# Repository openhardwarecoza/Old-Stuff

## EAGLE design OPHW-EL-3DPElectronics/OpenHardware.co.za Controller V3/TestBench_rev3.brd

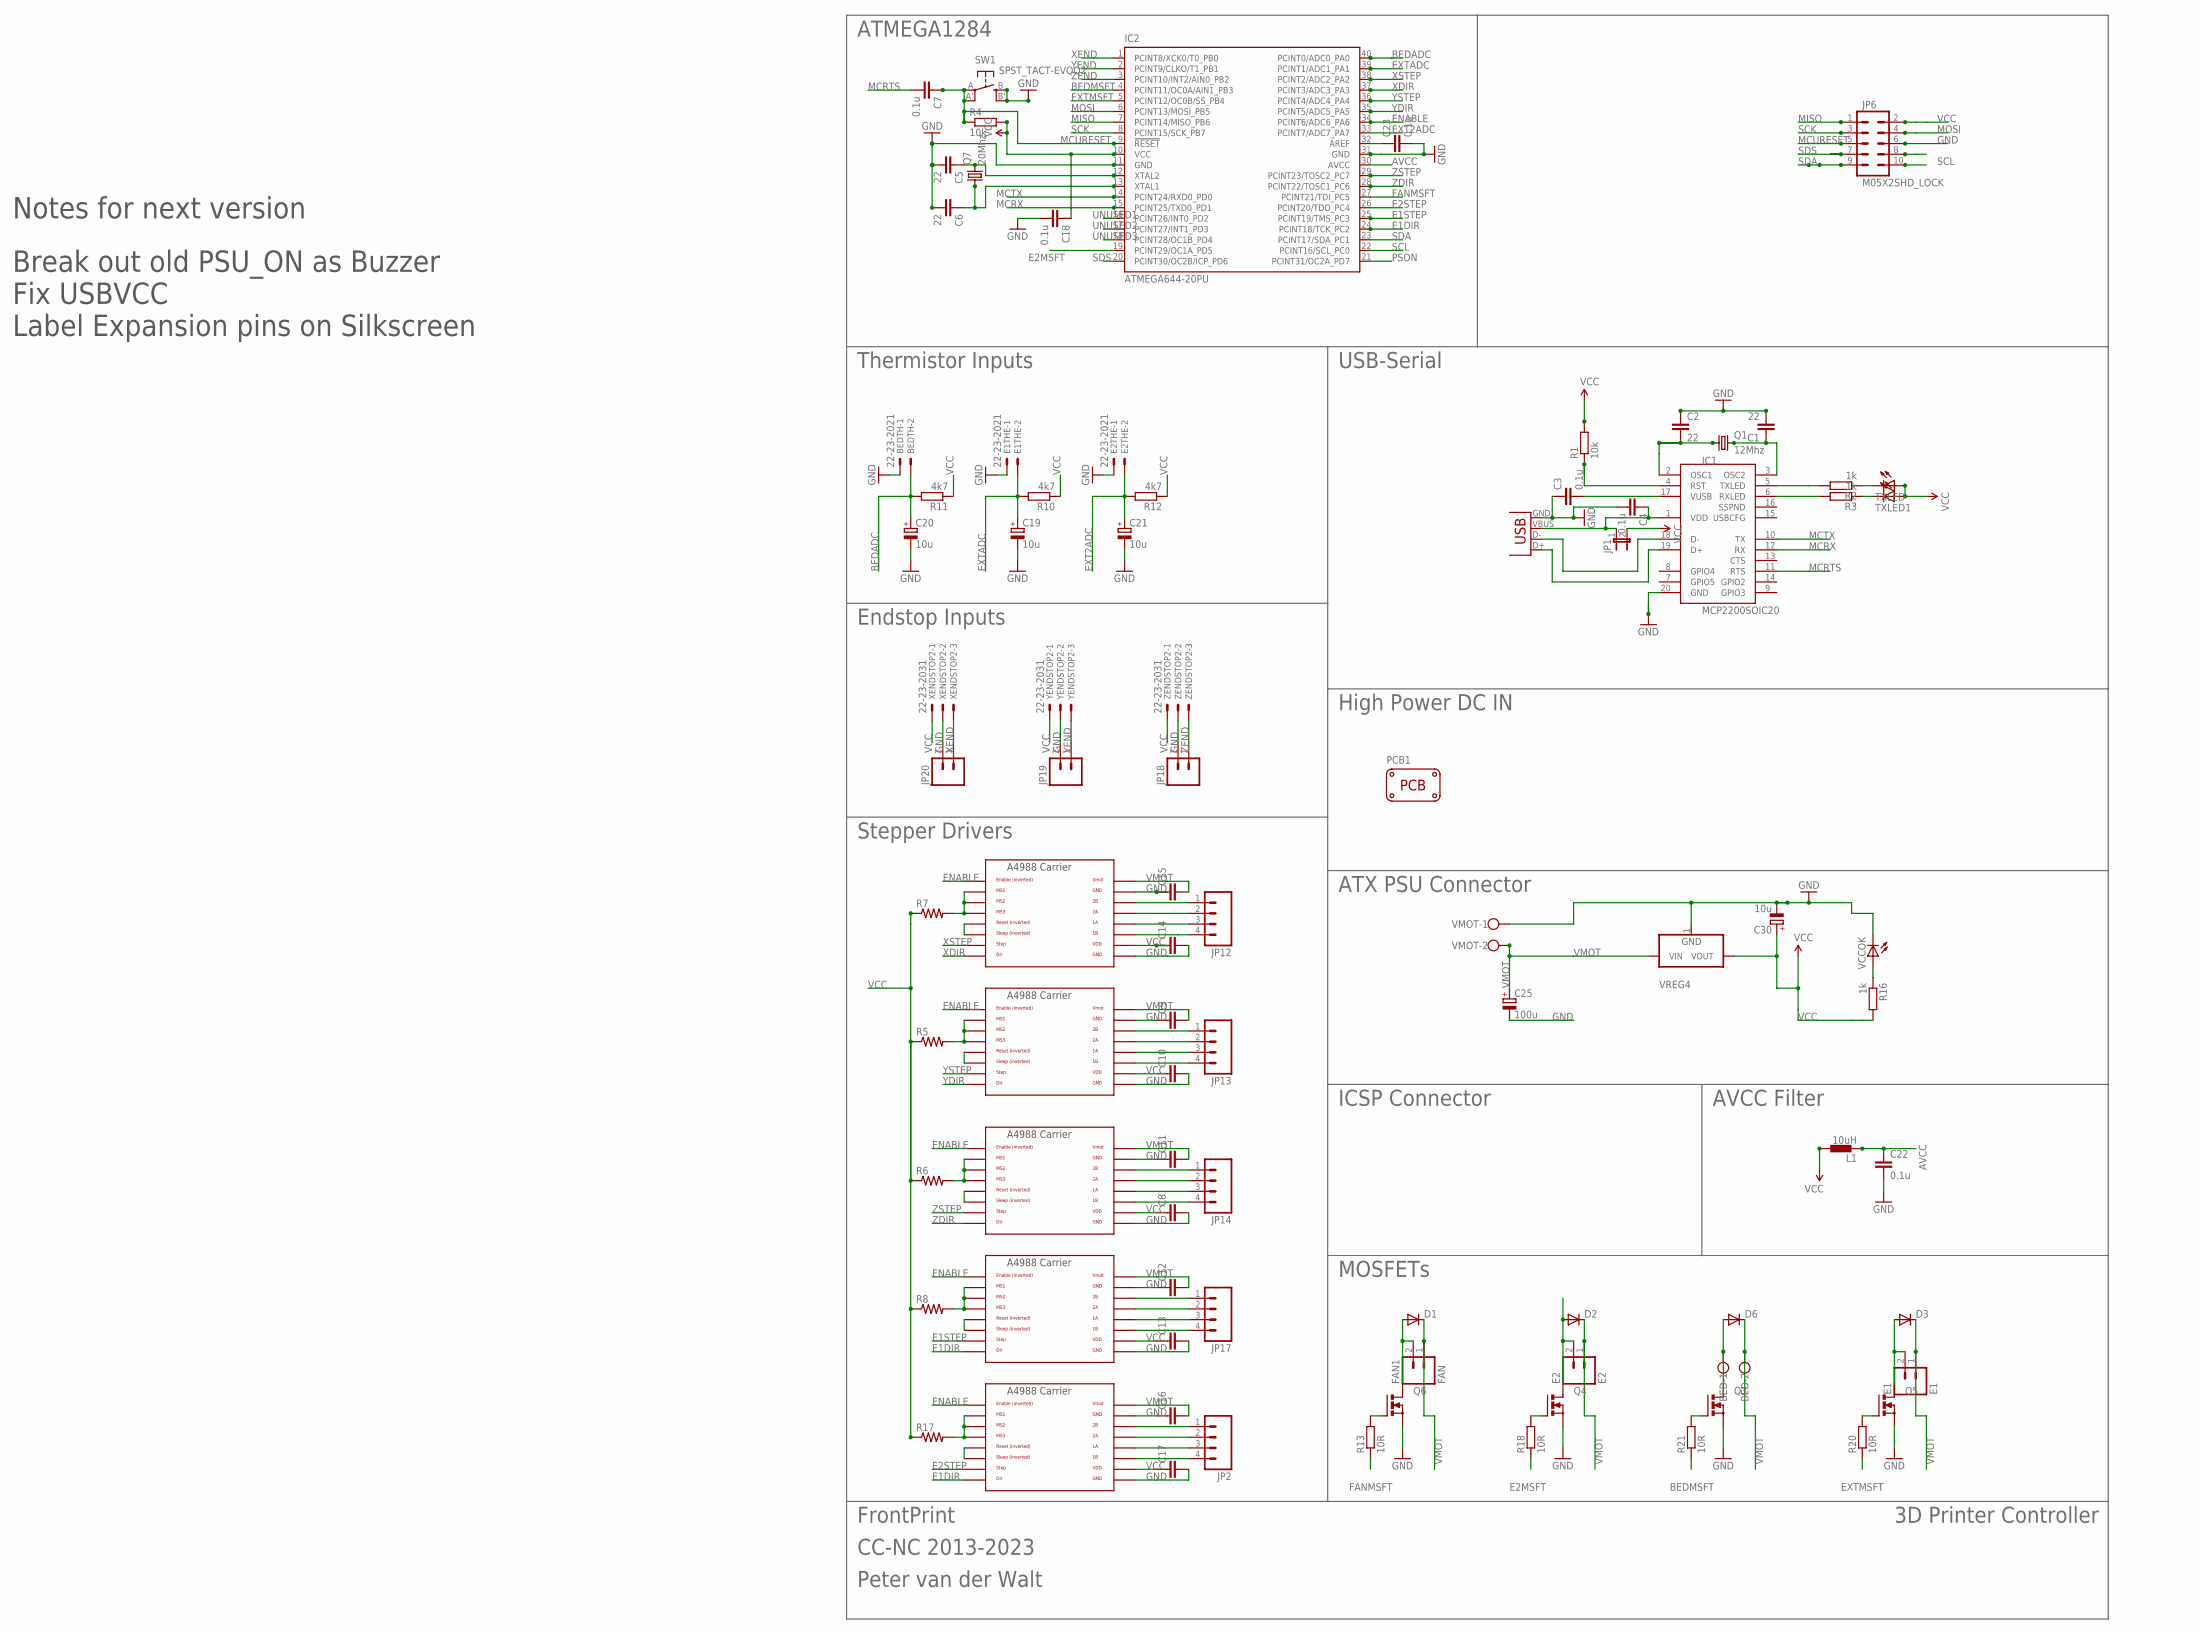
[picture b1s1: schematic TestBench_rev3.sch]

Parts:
BED: W237-102
BEDTH: 22-23-2021
C1, C2, C5, C6: 22; 1206
C3, C4, C7, C18, C22, C23: 0.1u; 1206
C8, C9, C10, C11, C12, C13, C14, C15, C16, C17: CAP1206; 1206
C19, C20, C21: 10u; E2,5-5
C25: 100u; E5-8,5
C30: 10u; E2-5
D1, D2, D3, D6: DIODESMA-ALT; SMA-DIODE_ALT
E1: E1; SCREWTERMINAL-3.5MM-2
E1POL, E2POL: POLOLU_A4983CARRIER; A4988BREAKOUT
E1THE, E2THE: 22-23-2021
E2: E2; SCREWTERMINAL-3.5MM-2
FAN1: FAN; SCREWTERMINAL-3.5MM-2
IC1: MCP2200SOIC20; SOIC20
IC2: ATMEGA644-20PU; DIL40
JP1: JUMPER-2PTH_LOCK; 1X02_LOCK
JP2, JP12, JP13, JP14, JP17: M04SCREW; SCREWTERMINAL-3.5MM-4
JP6: M05X2SHD_LOCK; 2X5-SHROUDED_LOCK
JP18, JP19, JP20: M023.5MM; SCREWTERMINAL-3.5MM-2
L1: 10uH; BL01RN1A
PCB1: PCB_DP_SQUARE-10X10; DP100100_V1
Q1: 12Mhz; HC49UP
Q3, Q4, Q5, Q6: PMOSFET_NTO220BV; TO220BV
Q7: 20Mhz; HC49UP
R1, R4: 10k; M1206
R2, R3, R16: 1k; M1206
R5, R6, R7, R8, R17: RESISTOR1206; 1206
R10, R11, R12: 4k7; M1206
R13, R18, R20, R21: 10R; M1206
SW1: SPST_TACT-EVQQ2; EVQ-Q2
TXLED, TXLED1: LEDSMT1206; 1206
VCCOK: LEDSMT1206; 1206
VMOT: W237-102; MPN 237-102
VREG4: VREG_3PINS-DPAK; DPAK
X1: USBPTH; USB-B-PTH
XENDSTOP2: 22-23-2031
XPOL: POLOLU_A4983CARRIER; A4988BREAKOUT
YENDSTOP2: 22-23-2031
YPOL: POLOLU_A4983CARRIER; A4988BREAKOUT
ZENDSTOP2: 22-23-2031
ZPOL: POLOLU_A4983CARRIER; A4988BREAKOUT

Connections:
AVCC: C22.1, IC2.30 (AVCC), L1.1
BEDADC: BEDTH.2, C20.+, IC2.40 (PCINT0/ADC0_PA0), R11.2
BEDMSFT: IC2.4 (PCINT11/OC0A/AIN1_PB3), R21.1
BEDOUT1: BED.1, D6.A, Q3.D
BEDOUT2: D3.A, E1.2, Q5.D
E1DIR: E1POL.DIR, E2POL.DIR, IC2.24 (PCINT18/TCK_PC2)
E1OUT1: D2.A, E2.2, Q4.D
E1STEP: E1POL.STEP, IC2.25 (PCINT19/TMS_PC3)
E2MSFT: IC2.19 (PCINT29/OC1A_PD5), R18.1
E2STEP: E2POL.STEP, IC2.26 (PCINT20/TDO_PC4)
ENABLE: E1POL.EN, E2POL.EN, IC2.34 (PCINT6/ADC6_PA6), XPOL.EN, YPOL.EN, ZPOL.EN
EXT2ADC: C21.+, E2THE.2, IC2.33 (PCINT7/ADC7_PA7), R12.2
EXTADC: C19.+, E1THE.2, IC2.39 (PCINT1/ADC1_PA1), R10.2
EXTMSFT: IC2.5 (PCINT12/OC0B/SS_PB4), R20.1
FANMSFT: IC2.27 (PCINT21/TDI_PC5), R13.1
FANOUT1: D1.A, FAN1.2, Q6.D
GND: BEDTH.1, C1.2, C2.1, C3.1, C4.2, C5.2, C6.2, C8.2, C9.1, C10.2, C11.1, C12.1, C13.2, C14.2, C15.1, C16.1, C17.2, C18.2, C19.-, C20.-, C21.-, C22.2, C23.2, C25.-, C30.-, E1POL.GND, E1POL.GND@0 (GND), E1THE.1, E2POL.GND, E2POL.GND@0 (GND), E2THE.1, IC1.20 (GND), IC2.11 (GND), IC2.31 (GND), JP6.6, JP18.2, JP19.2, JP20.2, Q3.S, Q4.S, Q5.S, Q6.S, SW1.B (S), SW1.B' (S1), VCCOK.C, VMOT.1, VREG4.1 (GND), X1.GND, XENDSTOP2.2, XPOL.GND, XPOL.GND@0 (GND), YENDSTOP2.2, YPOL.GND, YPOL.GND@0 (GND), ZENDSTOP2.2, ZPOL.GND, ZPOL.GND@0 (GND)
MCRTS: C7.2, IC1.11 (RTS)
MCRX: IC1.12 (RX), IC2.15 (PCINT25/TXD0_PD1)
MCTX: IC1.10 (TX), IC2.14 (PCINT24/RXD0_PD0)
MCURESET: C7.1, IC2.9 (!RESET), JP6.5, R4.1, SW1.A, SW1.A' (P1)
MISO: IC2.7 (PCINT14/MISO_PB6), JP6.1
MOSI: IC2.6 (PCINT13/MOSI_PB5), JP6.4
unnamed: C2.2, IC1.2 (OSC1), Q1.1
unnamed: C1.1, IC1.3 (OSC2), Q1.2
unnamed: IC1.5 (TXLED), R2.2
unnamed: IC1.18 (D-), X1.D-
unnamed: IC1.19 (D+), X1.D+
unnamed: IC1.6 (RXLED), R3.2
unnamed: C3.2, IC1.17 (VUSB)
unnamed: E2POL.RST, E2POL.SLP (SLEEP)
unnamed: R2.1, TXLED.C
unnamed: R3.1, TXLED1.C
unnamed: C5.1, IC2.12 (XTAL2), Q7.2
unnamed: C6.1, IC2.13 (XTAL1), Q7.1
unnamed: IC1.4 (RST), R1.1
unnamed: E1POL.RST, E1POL.SLP (SLEEP)
unnamed: ZPOL.RST, ZPOL.SLP (SLEEP)
unnamed: YPOL.RST, YPOL.SLP (SLEEP)
unnamed: XPOL.RST, XPOL.SLP (SLEEP)
unnamed: R7.2, XPOL.MS1, XPOL.MS2, XPOL.MS3
unnamed: R5.2, YPOL.MS1, YPOL.MS2, YPOL.MS3
unnamed: E1POL.MS1, E1POL.MS2, E1POL.MS3, R8.2
unnamed: R6.2, ZPOL.MS1, ZPOL.MS2, ZPOL.MS3
unnamed: E1POL.1B, JP17.4
unnamed: E1POL.1A, JP17.3
unnamed: E1POL.2A, JP17.2
unnamed: E1POL.2B, JP17.1
unnamed: JP14.4, ZPOL.1B
unnamed: JP14.3, ZPOL.1A
unnamed: JP14.2, ZPOL.2A
unnamed: JP14.1, ZPOL.2B
unnamed: JP13.1, YPOL.2B
unnamed: JP13.2, YPOL.2A
unnamed: JP13.3, YPOL.1A
unnamed: JP13.4, YPOL.1B
unnamed: JP12.4, XPOL.1B
unnamed: JP12.3, XPOL.1A
unnamed: JP12.2, XPOL.2A
unnamed: JP12.1, XPOL.2B
unnamed: E2POL.MS1, E2POL.MS2, E2POL.MS3, R17.2
unnamed: E2POL.1B, JP2.4
unnamed: E2POL.1A, JP2.3
unnamed: E2POL.2A, JP2.2
unnamed: E2POL.2B, JP2.1
unnamed: Q5.G, R20.2
unnamed: C23.1, IC2.32 (AREF)
unnamed: Q6.G, R13.2
unnamed: C4.1, IC1.1 (VDD), JP1.1, X1.VBUS
unnamed: Q4.G, R18.2
unnamed: R16.1, VCCOK.A
unnamed: Q3.G, R21.2
PSON: IC2.21 (PCINT31/OC2A_PD7)
SCK: IC2.8 (PCINT15/SCK_PB7), JP6.3
SCL: IC2.22 (PCINT16/SCL_PC0), JP6.10
SDA: IC2.23 (PCINT17/SDA_PC1), JP6.9
SDS: IC2.20 (PCINT30/OC2B/ICP_PD6), JP6.7
UNUSED1: IC2.16 (PCINT26/INT0_PD2)
UNUSED2: IC2.17 (PCINT27/INT1_PD3)
UNUSED3: IC2.18 (PCINT28/OC1B_PD4)
VCC: C8.1, C10.1, C13.1, C14.1, C17.1, C18.1, C30.+, E1POL.VDD, E2POL.VDD, IC2.10 (VCC), JP1.2, JP6.2, L1.2, R1.2, R4.2, R5.1, R6.1, R7.1, R8.1, R10.1, R11.1, R12.1, R16.2, R17.1, TXLED.A, TXLED1.A, VREG4.2 (VOUT), XENDSTOP2.1, XPOL.VDD, YENDSTOP2.1, YPOL.VDD, ZENDSTOP2.1, ZPOL.VDD
VMOT: BED.2, C9.2, C11.2, C12.2, C15.2, C16.2, C25.+, D1.C, D2.C, D3.C, D6.C, E1.1, E1POL.VMOT, E2.1, E2POL.VMOT, FAN1.1, VMOT.2, VREG4.3 (VIN), XPOL.VMOT, YPOL.VMOT, ZPOL.VMOT
XDIR: IC2.37 (PCINT3/ADC3_PA3), XPOL.DIR
XEND: IC2.1 (PCINT8/XCK0/T0_PB0), JP20.1, XENDSTOP2.3
XSTEP: IC2.38 (PCINT2/ADC2_PA2), XPOL.STEP
YDIR: IC2.35 (PCINT5/ADC5_PA5), YPOL.DIR
YEND: IC2.2 (PCINT9/CLKO/T1_PB1), JP19.1, YENDSTOP2.3
YSTEP: IC2.36 (PCINT4/ADC4_PA4), YPOL.STEP
ZDIR: IC2.28 (PCINT22/TOSC1_PC6), ZPOL.DIR
ZEND: IC2.3 (PCINT10/INT2/AIN0_PB2), JP18.1, ZENDSTOP2.3
ZSTEP: IC2.29 (PCINT23/TOSC2_PC7), ZPOL.STEP

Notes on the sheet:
Thermistor Inputs
Endstop Inputs
Stepper Drivers
USB-Serial
AVCC Filter
ATX PSU Connector
ICSP Connector
MOSFETs
High Power DC IN
ATMEGA1284
FrontPrint
CC-NC 2013-2023
Peter van der Walt
3D Printer Controller
Notes for next version
Break out old PSU_ON as Buzzer
Fix USBVCC
Label Expansion pins on Silkscreen

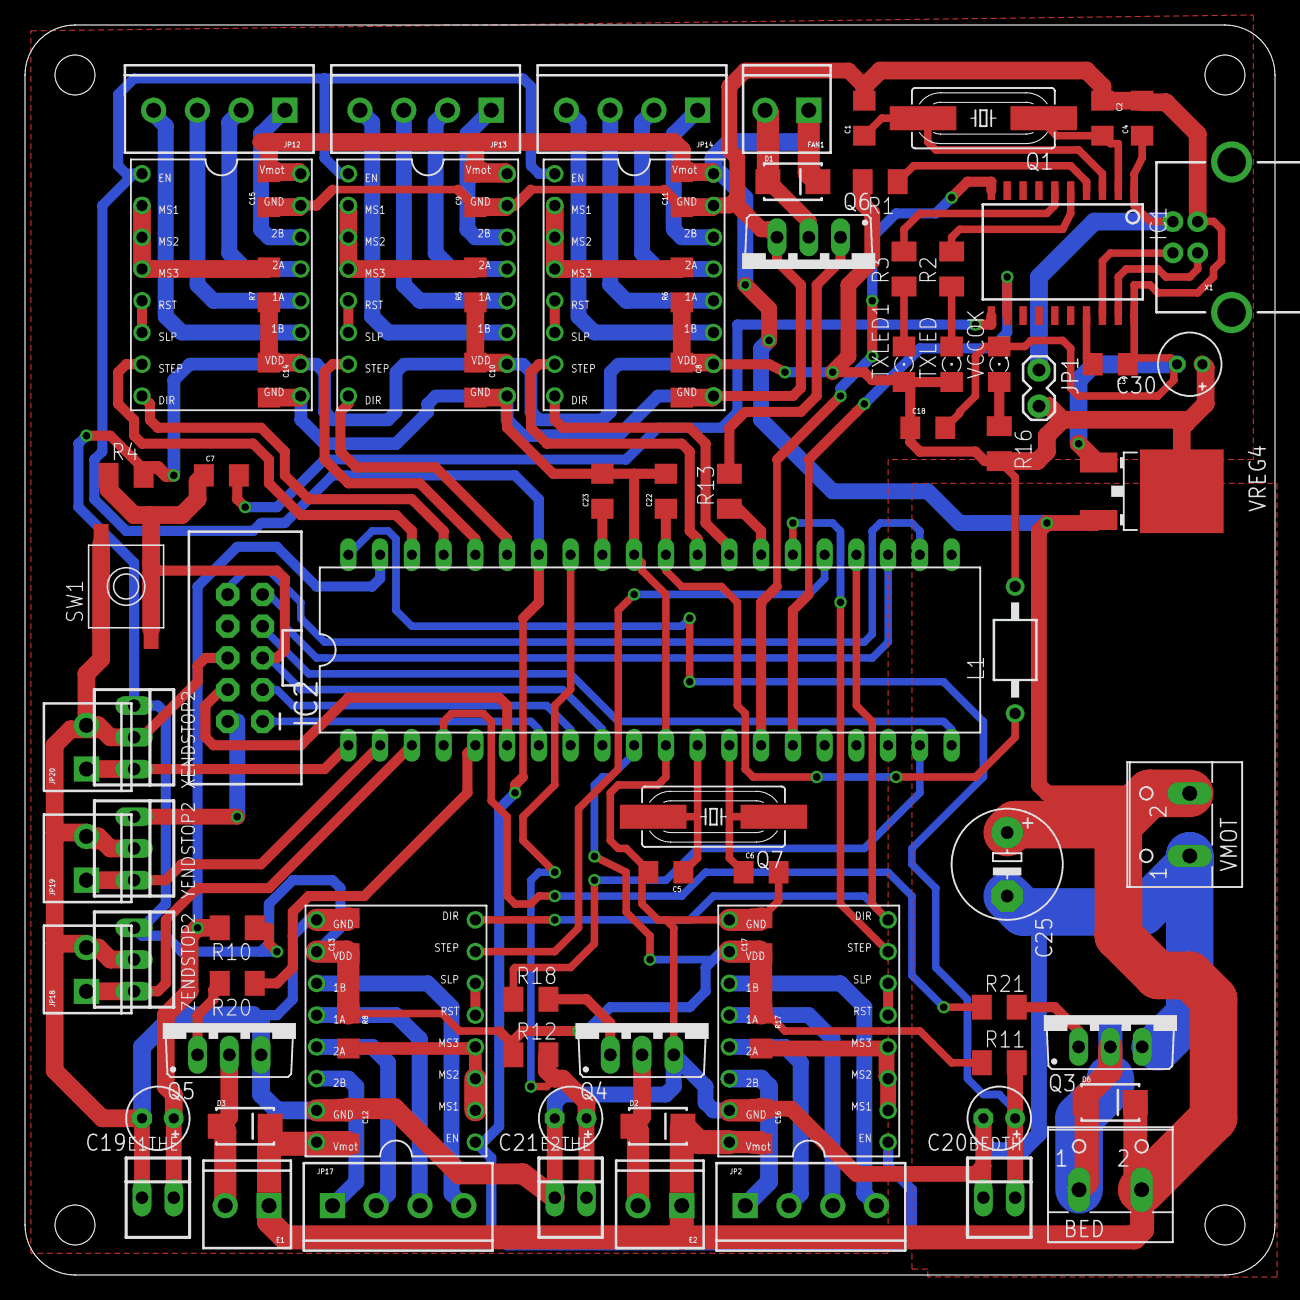
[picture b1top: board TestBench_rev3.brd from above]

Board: 2 copper layers, 100.0 x 100.0 mm, 88 parts (0 on the bottom side), 87 nets.

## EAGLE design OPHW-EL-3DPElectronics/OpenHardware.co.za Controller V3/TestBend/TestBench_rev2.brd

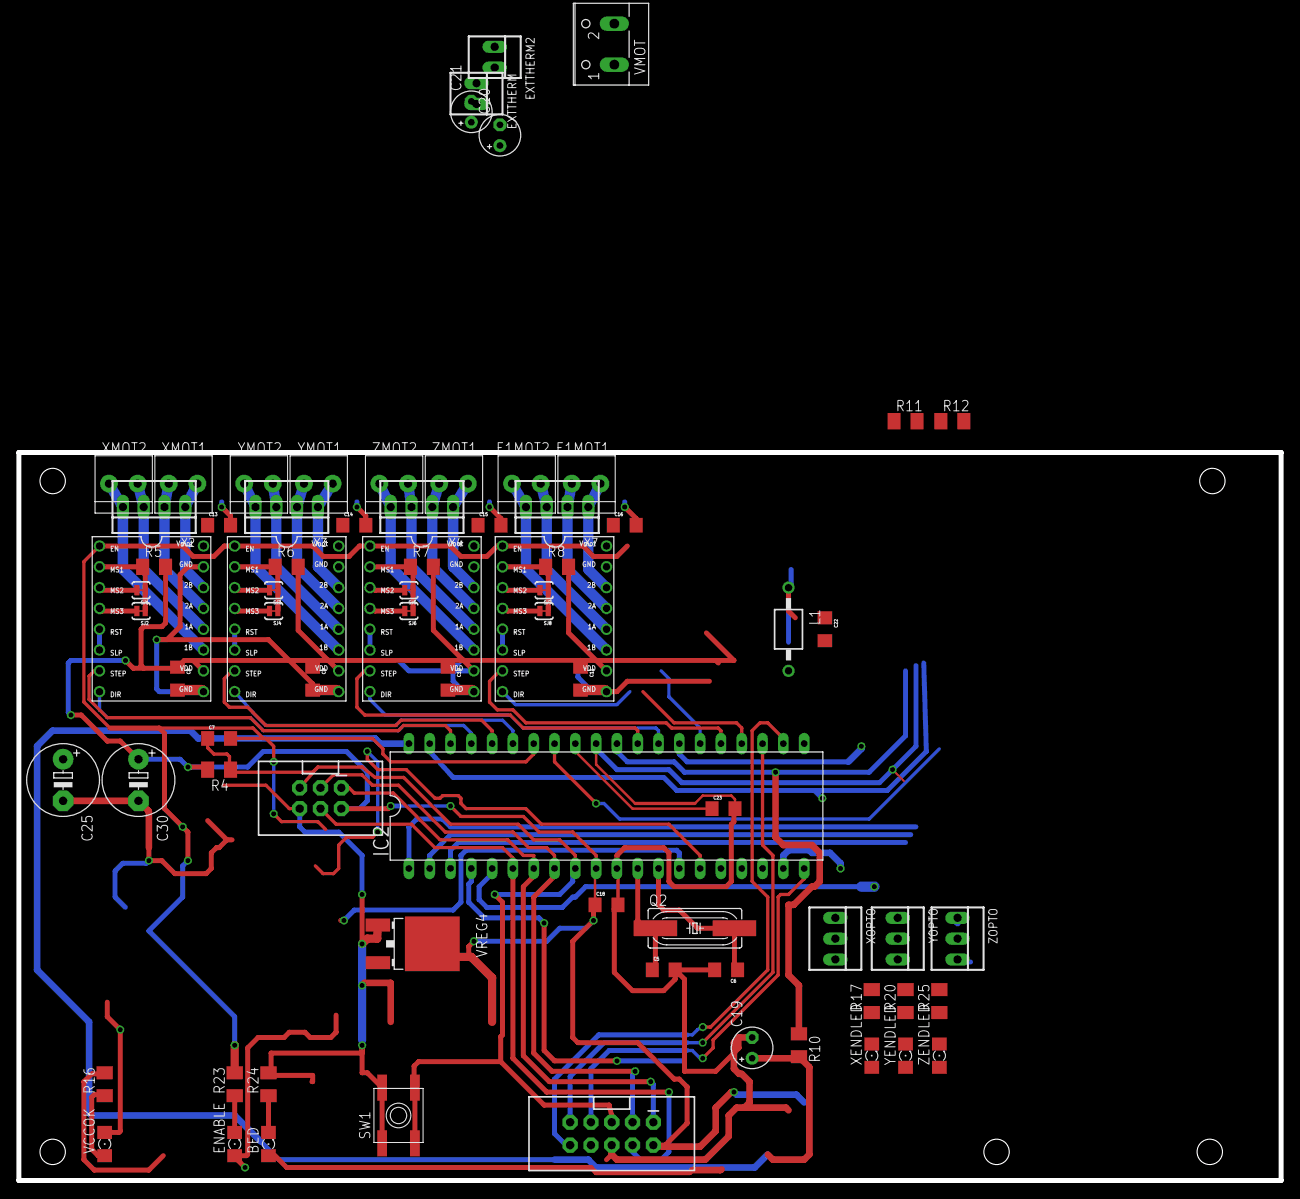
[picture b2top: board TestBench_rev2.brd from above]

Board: 2 copper layers, 154.1 x 88.9 mm, 81 parts (0 on the bottom side), 68 nets.

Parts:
BED: 1206
C5, C6: 22; 1206
C7, C8, C9, C10, C11, C13, C14, C15, C16, C18, C22, C23: 0.1u; 1206
C19, C20, C21: 10u; E2,5-5
C25, C30: 100u; E5-8,5
E1MOT1, E1MOT2: 1X2-3.5MM; 3.5MMTERM
ENABLE: 1206
EPOLOLU: POLOLU_A4983CARRIER; A4988BREAKOUT
EXTTHERM, EXTTHERM2: 22-23-2021
IC2: ATMEGA644-20PU; DIL40
J2: 2X3-SHROUDED
L1: 10uH; BL01RN1A
LCDCONNECTOR: M05X2SHD_LOCK; 2X5-SHROUDED_LOCK
Q2: 20mHz; HC49UP
R4: 10k; M1206
R5, R6, R7, R8: 1K; M1206
R10, R11, R12: 4k7; M1206
R16, R17, R20, R23, R24, R25: 1k; M1206
SJ1, SJ2, SJ3, SJ4, SJ5, SJ6, SJ7, SJ8: SOLDERJUMPERTRACE; SJ_2S-TRACE
SW1: SPST_TACT-EVQQ2; EVQ-Q2
U$1, U$5, U$6, U$7, U$8: 3MMHOLE
VCCOK: 1206
VMOT: W237-102
VREG4: DPAK
X2, X3, X4, X7: 22-23-2041
XENDLED: 1206
XMOT1, XMOT2: 1X2-3.5MM; 3.5MMTERM
XOPTO: 22-23-2031
XPOLOLU: POLOLU_A4983CARRIER; A4988BREAKOUT
YENDLED: 1206
YMOT1, YMOT2: 1X2-3.5MM; 3.5MMTERM
YOPTO: 22-23-2031
YPOLOLU: POLOLU_A4983CARRIER; A4988BREAKOUT
ZENDLED: 1206
ZMOT1, ZMOT2: 1X2-3.5MM; 3.5MMTERM
ZOPTO: 22-23-2031
ZPOLOLU: POLOLU_A4983CARRIER; A4988BREAKOUT

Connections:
AVCC: C22.1, IC2.30, L1.1, R10.1, R11.1, R12.1
BEDADC: C19.+, IC2.40, R10.2
BEDMSFT: BED.A, IC2.4
E1DIR: EPOLOLU.DIR, IC2.24
E1STEP: EPOLOLU.STEP, IC2.25
E11A: E1MOT2.1, EPOLOLU.1A, X7.3
E11B: E1MOT2.2, EPOLOLU.1B, X7.4
E12A: E1MOT1.2, EPOLOLU.2A, X7.2
E12B: E1MOT1.1, EPOLOLU.2B, X7.1
ENABLE: EPOLOLU.EN, IC2.34, R23.2, XPOLOLU.EN, YPOLOLU.EN, ZPOLOLU.EN
EXT2ADC: C21.+, EXTTHERM2.2, IC2.33, R12.2
EXTADC: C20.+, EXTTHERM.2, IC2.39, R11.2
GND: C5.2, C6.2, C8.2, C9.2, C10.2, C11.2, C13.2, C14.2, C15.2, C16.2, C18.2, C19.-, C20.-, C21.-, C22.2, C23.2, C25.-, C30.-, EPOLOLU.GND, EPOLOLU.GND@0, EXTTHERM.1, EXTTHERM2.1, IC2.11, IC2.31, J2.6, LCDCONNECTOR.6, R24.2, SW1.B, SW1.B', VCCOK.C, VMOT.1, VREG4.1, XOPTO.2, XPOLOLU.GND, XPOLOLU.GND@0, YOPTO.2, YPOLOLU.GND, YPOLOLU.GND@0, ZOPTO.2, ZPOLOLU.GND, ZPOLOLU.GND@0
MCURESET: C7.1, IC2.9, J2.5, LCDCONNECTOR.5, R4.1, SW1.A, SW1.A'
MISO: IC2.7, J2.1, LCDCONNECTOR.1
MOSI: IC2.6, J2.4, LCDCONNECTOR.4
unnamed: C5.1, IC2.12, Q2.1
unnamed: C6.1, IC2.13, Q2.2
unnamed: R7.1, SJ5.1, SJ6.1, ZPOLOLU.MS1
unnamed: SJ6.2, ZPOLOLU.MS3
unnamed: SJ5.2, ZPOLOLU.MS2
unnamed: EPOLOLU.MS2, SJ7.2
unnamed: EPOLOLU.MS3, SJ8.2
unnamed: EPOLOLU.MS1, R8.1, SJ7.1, SJ8.1
unnamed: SJ3.2, YPOLOLU.MS2
unnamed: SJ4.2, YPOLOLU.MS3
unnamed: R6.1, SJ3.1, SJ4.1, YPOLOLU.MS1
unnamed: SJ1.2, XPOLOLU.MS2
unnamed: SJ2.2, XPOLOLU.MS3
unnamed: R5.1, SJ1.1, SJ2.1, XPOLOLU.MS1
unnamed: XPOLOLU.RST, XPOLOLU.SLP
unnamed: YPOLOLU.RST, YPOLOLU.SLP
unnamed: ZPOLOLU.RST, ZPOLOLU.SLP
unnamed: EPOLOLU.RST, EPOLOLU.SLP
unnamed: X4.4, ZMOT2.2, ZPOLOLU.1B
unnamed: X4.3, ZMOT2.1, ZPOLOLU.1A
unnamed: X4.2, ZMOT1.2, ZPOLOLU.2A
unnamed: X4.1, ZMOT1.1, ZPOLOLU.2B
unnamed: X3.4, YMOT2.2, YPOLOLU.1B
unnamed: X3.3, YMOT2.1, YPOLOLU.1A
unnamed: X3.2, YMOT1.2, YPOLOLU.2A
unnamed: X3.1, YMOT1.1, YPOLOLU.2B
unnamed: X2.4, XMOT2.2, XPOLOLU.1B
unnamed: X2.3, XMOT2.1, XPOLOLU.1A
unnamed: X2.2, XMOT1.2, XPOLOLU.2A
unnamed: X2.1, XMOT1.1, XPOLOLU.2B
unnamed: C23.1, IC2.32
unnamed: R17.1, XENDLED.C
unnamed: BED.C, R24.1
unnamed: R20.1, YENDLED.C
unnamed: R25.1, ZENDLED.C
unnamed: R16.1, VCCOK.A
unnamed: ENABLE.C, R23.1
SCK: IC2.8, J2.3, LCDCONNECTOR.3
SCL: IC2.22, LCDCONNECTOR.10
SDA: IC2.23, LCDCONNECTOR.9
SDS: IC2.20, LCDCONNECTOR.7
VCC: C8.1, C9.1, C10.1, C11.1, C18.1, C30.+, ENABLE.A, EPOLOLU.VDD, IC2.10, J2.2, L1.2, LCDCONNECTOR.2, R4.2, R5.2, R6.2, R7.2, R8.2, R16.2, VREG4.2, XENDLED.A, XOPTO.1, XPOLOLU.VDD, YENDLED.A, YOPTO.1, YPOLOLU.VDD, ZENDLED.A, ZOPTO.1, ZPOLOLU.VDD
VMOT: C13.1, C14.1, C15.1, C16.1, C25.+, EPOLOLU.VMOT, VMOT.2, VREG4.3, XPOLOLU.VMOT, YPOLOLU.VMOT, ZPOLOLU.VMOT
XDIR: IC2.37, XPOLOLU.DIR
XEND: IC2.1, R17.2, XOPTO.3
XSTEP: IC2.38, XPOLOLU.STEP
YDIR: IC2.35, YPOLOLU.DIR
YEND: IC2.2, R20.2, YOPTO.3
YSTEP: IC2.36, YPOLOLU.STEP
ZDIR: IC2.28, ZPOLOLU.DIR
ZEND: IC2.3, R25.2, ZOPTO.3
ZSTEP: IC2.29, ZPOLOLU.STEP

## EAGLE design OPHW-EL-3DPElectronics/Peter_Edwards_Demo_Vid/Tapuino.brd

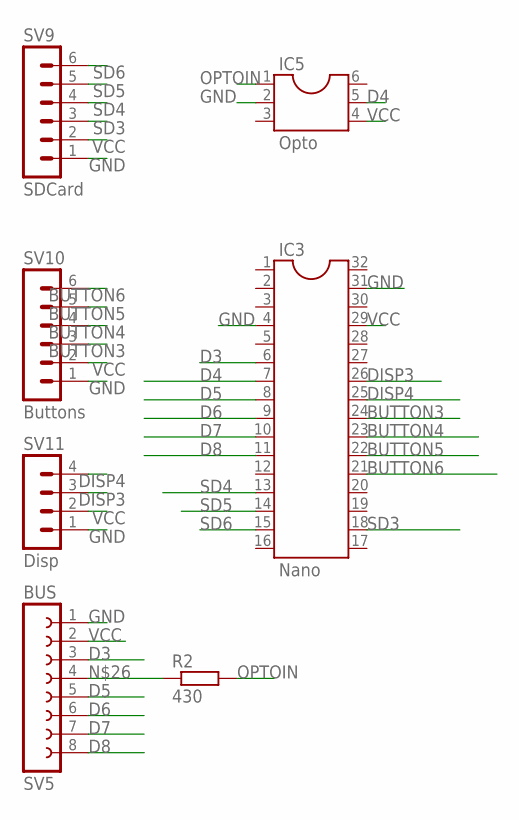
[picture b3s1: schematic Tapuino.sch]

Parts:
IC3: Nano; DIL32
IC5: Opto; DIL06
R2: 430; 0207/10
SV5: BUS; FE08
SV9: SDCard; MA06-1
SV10: Buttons; MA06-1
SV11: Disp; MA04-1

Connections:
BUTTON3: IC3.24, SV10.3
BUTTON4: IC3.23, SV10.4
BUTTON5: IC3.22, SV10.5
BUTTON6: IC3.21, SV10.6
D3: IC3.6, SV5.3
D4: IC3.7, IC5.5
D5: IC3.8, SV5.5
D6: IC3.9, SV5.6
D7: IC3.10, SV5.7
D8: IC3.11, SV5.8
DISP3: IC3.26, SV11.3
DISP4: IC3.25, SV11.4
GND: IC3.4, IC3.31, IC5.2, SV5.1, SV9.1, SV10.1, SV11.1
unnamed: R2.1, SV5.4
OPTOIN: IC5.1, R2.2
SD3: IC3.18, SV9.3
SD4: IC3.13, SV9.4
SD5: IC3.14, SV9.5
SD6: IC3.15, SV9.6
VCC: IC3.29, IC5.4, SV5.2, SV9.2, SV10.2, SV11.2

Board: 2 copper layers, 7 parts (0 on the bottom side), 20 nets, no tracks yet.

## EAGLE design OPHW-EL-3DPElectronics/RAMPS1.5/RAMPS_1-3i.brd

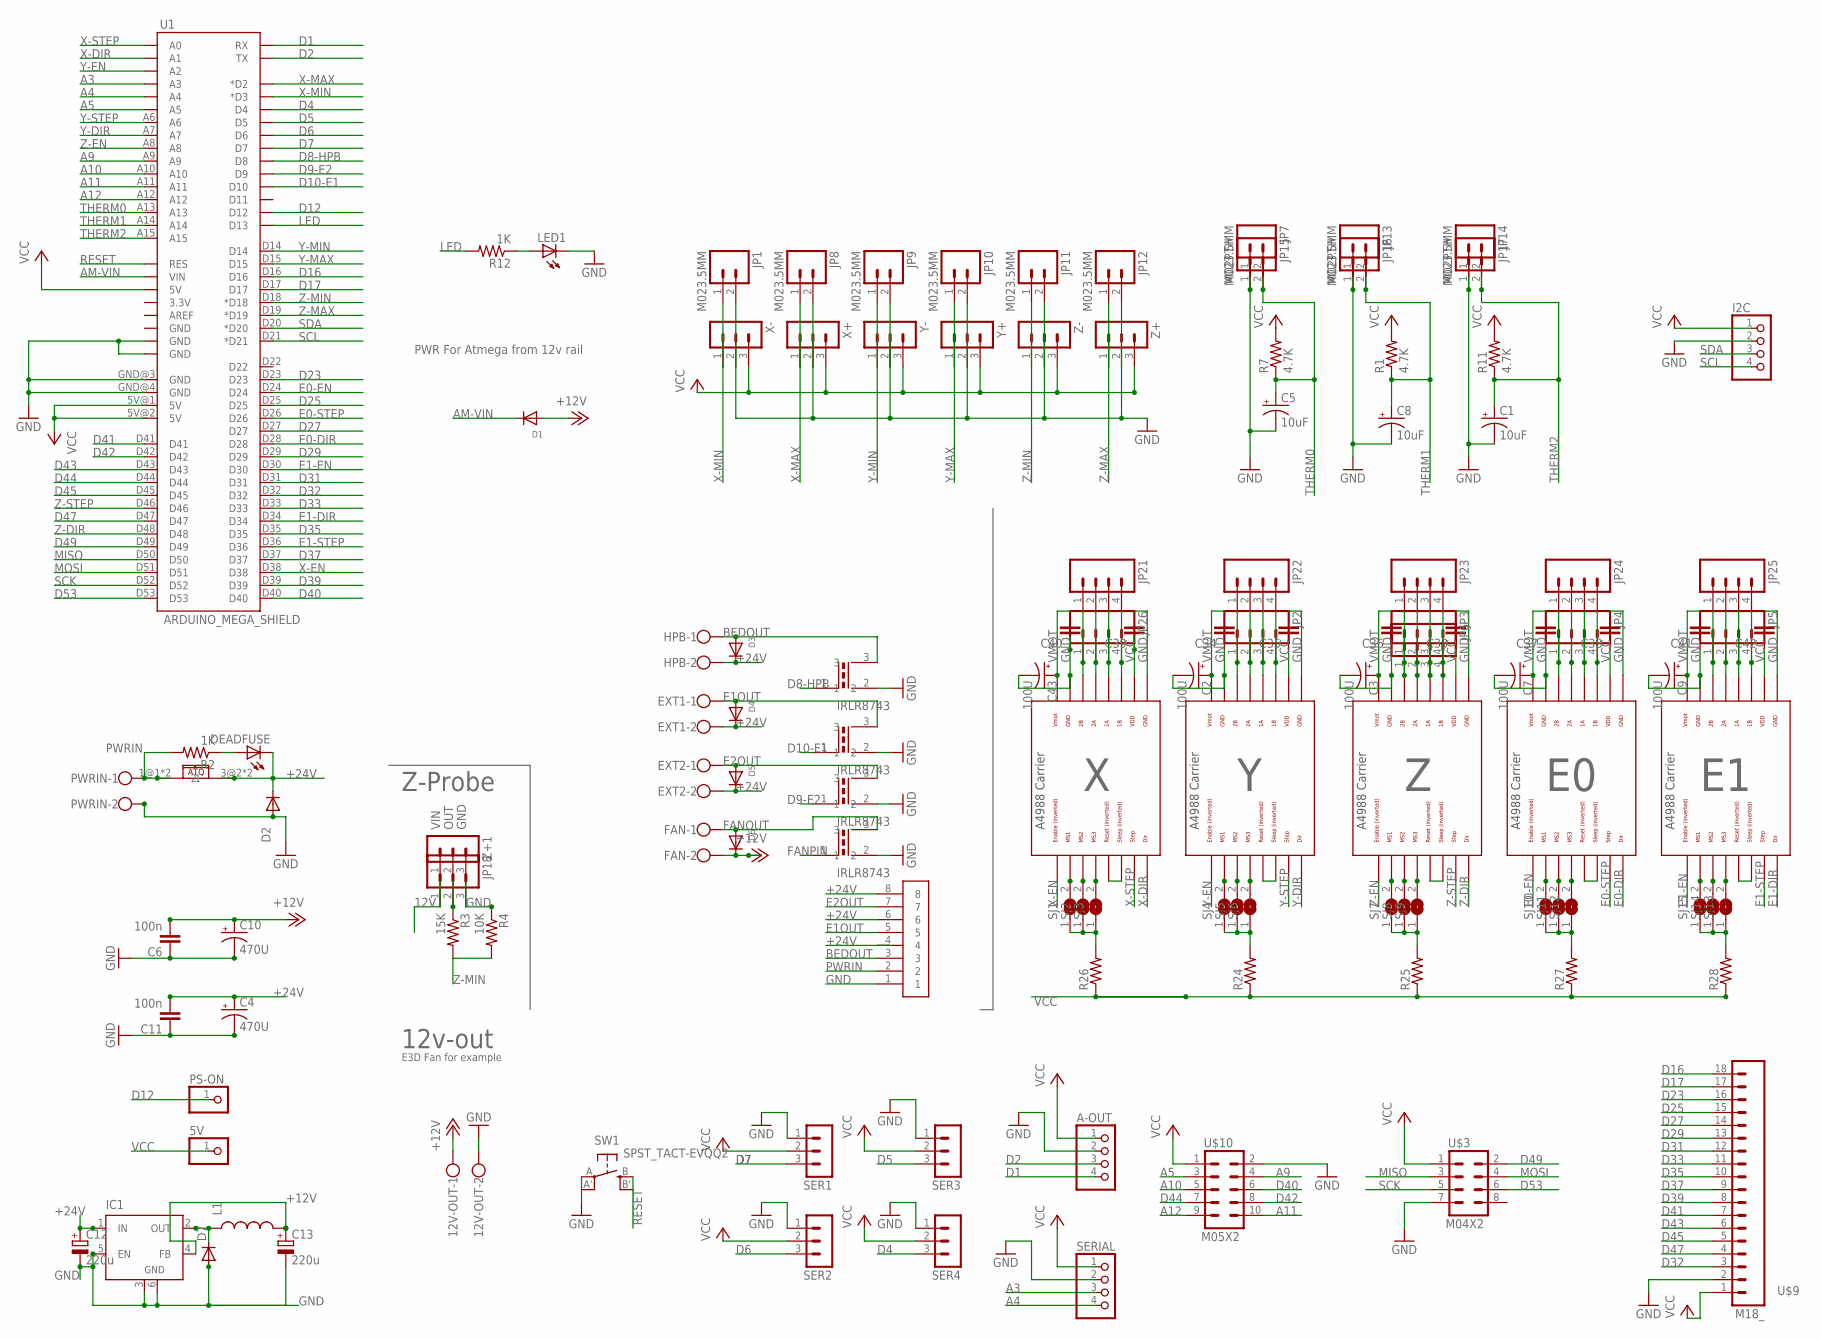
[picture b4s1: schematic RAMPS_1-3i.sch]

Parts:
5V: PINHD-1X1; 1X01
12V-OUT: W237-102
A-OUT: PINHD-1X4; 1X04
C1, C5, C8: 10uF; PANASONIC_C
C2, C3, C7, C9, C43: 100U; PANASONIC_D
C4, C10: 470U; PANASONIC_D
C6, C11: 100n; 1206
C12, C13: 220u; 153CLV-0605
C33, C34, C35, C36, C37, C38, C39, C40, C41, C42: CAP1206; 1206
D1, D2, D3, D4, D5, D6: DIODESMA; SMADIODE
D7: DIODE-DO-214AC; DO-214AC
DEADFUSE: LEDCHIPLED_1206; CHIPLED_1206
E1POL1, E2POL1: POLOLU_A4983CARRIER; A4988BREAKOUT
EXT1, EXT2: W237-102
FAN: W237-102
HPB: W237-102
I2C: PINHD-1X4; 1X04
IC1: LM2596S; TO263-5
JP1, JP7, JP8, JP9, JP10, JP11, JP12, JP13, JP14: M023.5MM; SCREWTERMINAL-3.5MM-2
JP2, JP3, JP4, JP5, JP6, JP26: M04PTH; 1X04
JP15, JP16, JP17: M02PTH; 1X02
JP18: M03SCREW_LOCK; SCREWTERMINAL-3.5MM-3_LOCK.007S
JP21, JP22, JP23, JP24, JP25: M04SCREW; SCREWTERMINAL-3.5MM-4
L1: INDUCTORPWR; CDRH125
LED1: LED3MM
PS-ON: PINHD-1X1; 1X01
PWRIN: W237-102
R1, R7, R11: 4.7K; M1206
R2, R12: 1K; M1206
R3: 15K; M1206
R4: 10K; M1206
R24, R25, R26, R27, R28: RESISTOR1206; 1206
SER1, SER2, SER3, SER4: 3PIN-HEADER
SERIAL: PINHD-1X4; 1X04
SJ1, SJ2, SJ3, SJ4, SJ5, SJ6, SJ7, SJ8, SJ9, SJ10, SJ11, SJ12, SJ13, SJ14, SJ15: SJ
SW1: SPST_TACT-EVQQ2; EVQ-Q2
U1: ARDUINO_MEGA_SHIELD
U$1, U$2, U$11, U$12: IRLR8743; TO263
U$3: M04X2; 2X4
U$4: XY825A-8P
U$5: CQ-121; CQ121
U$9: M18_; 1X18
U$10: M05X2; 2X5
X+: 3PIN-HEADER
X-: 3PIN-HEADER
XPOL1: POLOLU_A4983CARRIER; A4988BREAKOUT
Y+: 3PIN-HEADER
Y-: 3PIN-HEADER
YPOL1: POLOLU_A4983CARRIER; A4988BREAKOUT
Z+, Z+1: 3PIN-HEADER
Z-: 3PIN-HEADER
ZPOL1: POLOLU_A4983CARRIER; A4988BREAKOUT

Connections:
12V: JP18.1, Z+1.1
+12V: 12V-OUT.1, C6.2, C10.+, C13.+, D1.A, D6.C, FAN.2, IC1.4 (FB), L1.2
+24V: C4.+, C11.2, C12.+, D2.C, D3.C, D4.C, D5.C, DEADFUSE.C, EXT1.2, EXT2.2, HPB.2, IC1.1 (IN), U$4.6, U$4.8, U$5.3@2 (2), U$5.4@2 (2)
A3: SERIAL.3, U1.A3
A4: SERIAL.4, U1.A4
A5: U1.A5, U$10.3
A9: U1.A9, U$10.4
A10: U1.A10, U$10.5
A11: U1.A11, U$10.10
A12: U1.A12, U$10.9
AM-VIN: D1.C, U1.VIN
BEDOUT: D3.A, HPB.1, U$2.3, U$4.3
D1: A-OUT.4, U1.RX
D2: A-OUT.3, U1.TX
D4: SER4.3, U1.D4
D5: SER3.3, U1.D5
D6: SER2.3, U1.D6
D7: SER1.3, U1.D7
D8-HPB: U1.D8, U$2.1 (2)
D9-E2: U1.D9, U$11.1 (2)
D10-E1: U1.D10, U$12.1 (2)
D12: PS-ON.1, U1.D12
D16: U1.D16, U$9.18
D17: U1.D17, U$9.17
D23: U1.D23, U$9.16
D25: U1.D25, U$9.15
D27: U1.D27, U$9.14
D29: U1.D29, U$9.13
D31: U1.D31, U$9.12
D32: U1.D32, U$9.3
D33: U1.D33, U$9.11
D35: U1.D35, U$9.10
D37: U1.D37, U$9.9
D39: U1.D39, U$9.8
D40: U1.D40, U$10.6
D41: U1.D41, U$9.7
D42: U1.D42, U$10.8
D43: U1.D43, U$9.6
D44: U1.D44, U$10.7
D45: U1.D45, U$9.5
D47: U1.D47, U$9.4
D49: U1.D49, U$3.2
D53: U1.D53, U$3.6
E0-DIR: E1POL1.DIR, U1.D28
E0-EN: E1POL1.EN, U1.D24
E0-STEP: E1POL1.STEP, U1.D26
E1-DIR: E2POL1.DIR, U1.D34
E1-EN: E2POL1.EN, U1.D30
E1-STEP: E2POL1.STEP, U1.D36
E1OUT: D4.A, EXT1.1, U$4.5, U$12.3
E2OUT: D5.A, EXT2.1, U$4.7, U$11.3
FANOUT: D6.A, FAN.1, U$1.3
FANPIN: U$1.1 (2)
GND: 12V-OUT.2, A-OUT.2, C1.-, C2.-, C3.-, C4.-, C5.-, C6.1, C7.-, C8.-, C9.-, C10.-, C11.1, C12.-, C13.-, C33.2, C34.1, C35.2, C36.1, C37.1, C38.2, C39.2, C40.1, C41.1, C42.2, C43.-, D2.A, D7.2 (A), E1POL1.GND, E1POL1.GND@0 (GND), E2POL1.GND, E2POL1.GND@0 (GND), I2C.2, IC1.3 (GND), IC1.5 (EN), IC1.6 (GND), JP1.2, JP7.1, JP8.2, JP9.2, JP10.2, JP11.2, JP12.2, JP13.1, JP14.1, JP15.1, JP16.1, JP17.1, JP18.3, LED1.K (C), PWRIN.2, R4.1, SER1.1, SER2.1, SER3.1, SER4.1, SERIAL.2, SW1.A, SW1.A' (P1), U1.GND@0 (GND), U1.GND@1 (GND), U1.GND@3 (GND), U1.GND@4 (GND), U$1.2 (1), U$2.2 (1), U$3.7, U$4.1, U$9.2, U$10.2, U$11.2 (1), U$12.2 (1), X+.2, X-.2, XPOL1.GND, XPOL1.GND@0 (GND), Y+.2, Y-.2, YPOL1.GND, YPOL1.GND@0 (GND), Z+.2, Z+1.3, Z-.2, ZPOL1.GND, ZPOL1.GND@0 (GND)
LED: R12.2, U1.D13
MISO: U1.D50, U$3.3
MOSI: U1.D51, U$3.4
unnamed: D7.1 (C), IC1.2 (OUT), L1.1
unnamed: DEADFUSE.A, R2.1
unnamed: SJ2.2, XPOL1.MS2
unnamed: SJ1.2, XPOL1.MS1
unnamed: SJ4.2, YPOL1.MS1
unnamed: SJ5.2, YPOL1.MS2
unnamed: SJ7.2, ZPOL1.MS1
unnamed: SJ8.2, ZPOL1.MS2
unnamed: SJ9.2, ZPOL1.MS3
unnamed: SJ6.2, YPOL1.MS3
unnamed: SJ3.2, XPOL1.MS3
unnamed: E2POL1.MS2, SJ14.2
unnamed: E2POL1.MS3, SJ13.2
unnamed: E2POL1.MS1, SJ15.2
unnamed: E1POL1.MS3, SJ12.2
unnamed: E1POL1.MS1, SJ10.2
unnamed: E1POL1.MS2, SJ11.2
unnamed: LED1.A, R12.1
unnamed: E1POL1.RST, E1POL1.SLP (SLEEP)
unnamed: ZPOL1.RST, ZPOL1.SLP (SLEEP)
unnamed: YPOL1.RST, YPOL1.SLP (SLEEP)
unnamed: XPOL1.RST, XPOL1.SLP (SLEEP)
unnamed: R26.2, SJ1.1, SJ2.1, SJ3.1
unnamed: R24.2, SJ4.1, SJ5.1, SJ6.1
unnamed: R27.2, SJ10.1, SJ11.1, SJ12.1
unnamed: R25.2, SJ7.1, SJ8.1, SJ9.1
unnamed: E1POL1.1B, JP4.4, JP24.4
unnamed: E1POL1.1A, JP4.3, JP24.3
unnamed: E1POL1.2A, JP4.2, JP24.2
unnamed: E1POL1.2B, JP4.1, JP24.1
unnamed: JP3.4, JP6.4, JP23.4, ZPOL1.1B
unnamed: JP3.3, JP6.3, JP23.3, ZPOL1.1A
unnamed: JP3.2, JP6.2, JP23.2, ZPOL1.2A
unnamed: JP3.1, JP6.1, JP23.1, ZPOL1.2B
unnamed: JP2.1, JP22.1, YPOL1.2B
unnamed: JP2.2, JP22.2, YPOL1.2A
unnamed: JP2.3, JP22.3, YPOL1.1A
unnamed: JP2.4, JP22.4, YPOL1.1B
unnamed: JP21.4, JP26.4, XPOL1.1B
unnamed: JP21.3, JP26.3, XPOL1.1A
unnamed: JP21.2, JP26.2, XPOL1.2A
unnamed: JP21.1, JP26.1, XPOL1.2B
unnamed: E2POL1.RST, E2POL1.SLP (SLEEP)
unnamed: R28.2, SJ13.1, SJ14.1, SJ15.1
unnamed: E2POL1.1B, JP5.4, JP25.4
unnamed: E2POL1.1A, JP5.3, JP25.3
unnamed: E2POL1.2A, JP5.2, JP25.2
unnamed: E2POL1.2B, JP5.1, JP25.1
PWRIN: PWRIN.1, R2.2, U$4.2, U$5.1@1 (1), U$5.2@1 (1)
RESET: SW1.B (S), SW1.B' (S1), U1.RES
SCK: U1.D52, U$3.5
SCL: I2C.4, U1.D21 (*D21)
SDA: I2C.3, U1.D20 (*D20)
SENSOROUT: JP18.2, R3.1, Z+1.2
THERM0: C5.+, JP7.2, JP15.2, R7.1, U1.A13
THERM1: C8.+, JP13.2, JP16.2, R1.1, U1.A14
THERM2: C1.+, JP14.2, JP17.2, R11.1, U1.A15
VCC: 5V.1, A-OUT.1, C33.1, C35.1, C38.1, C39.1, C42.1, E1POL1.VDD, E2POL1.VDD, I2C.1, R1.2, R7.2, R11.2, R24.1, R25.1, R26.1, R27.1, R28.1, SER1.2, SER2.2, SER3.2, SER4.2, SERIAL.1, U1.5V@0 (5V), U1.5V@1 (5V), U1.5V@2 (5V), U$3.1, U$9.1, U$10.1, X+.3, X-.3, XPOL1.VDD, Y+.3, Y-.3, YPOL1.VDD, Z+.3, Z-.3, ZPOL1.VDD
VMOT: C2.+, C3.+, C7.+, C9.+, C34.2, C36.2, C37.2, C40.2, C41.2, C43.+, E1POL1.VMOT, E2POL1.VMOT, XPOL1.VMOT, YPOL1.VMOT, ZPOL1.VMOT
X-DIR: U1.A1, XPOL1.DIR
X-EN: U1.D38, XPOL1.EN
X-MAX: JP8.1, U1.D2 (*D2), X+.1
X-MIN: JP1.1, U1.D3 (*D3), X-.1
X-STEP: U1.A0, XPOL1.STEP
Y-DIR: U1.A7, YPOL1.DIR
Y-EN: U1.A2, YPOL1.EN
Y-MAX: JP10.1, U1.D15, Y+.1
Y-MIN: JP9.1, U1.D14, Y-.1
Y-STEP: U1.A6, YPOL1.STEP
Z-DIR: U1.D48, ZPOL1.DIR
Z-EN: U1.A8, ZPOL1.EN
Z-MAX: JP12.1, U1.D19 (*D19), Z+.1
Z-MIN: JP11.1, R3.2, R4.2, U1.D18 (*D18), Z-.1
Z-STEP: U1.D46, ZPOL1.STEP

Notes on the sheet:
PWR For Atmega from 12v rail
12v-out
E3D Fan for example
Z-Probe
VIN
OUT
GND

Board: 2 copper layers, 124 parts (0 on the bottom side), 130 nets, no tracks yet.

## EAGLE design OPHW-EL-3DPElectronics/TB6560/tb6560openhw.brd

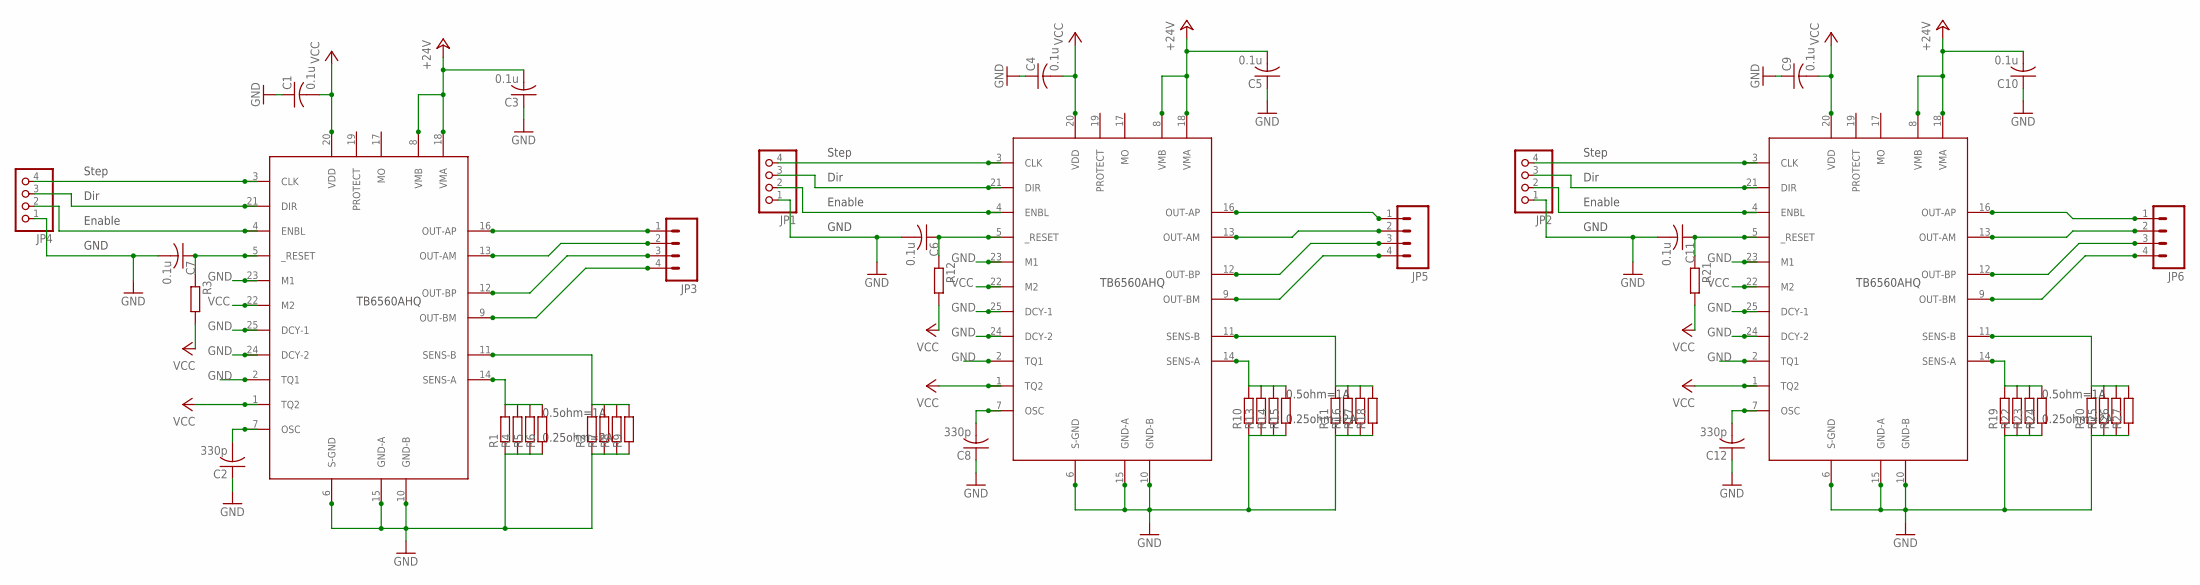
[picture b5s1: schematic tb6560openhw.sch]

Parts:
C1, C3, C4, C5, C6, C7, C9, C10, C11: 0.1u; C1206K
C2, C8, C12: 330p; C1206K
JP1, JP2, JP4: PINHD-1X4; 1X04
JP3, JP5, JP6: M04SCREW; SCREWTERMINAL-3.5MM-4
R1, R2, R4, R5, R6, R7, R8, R9, R10, R11, R13, R14, R15, R16, R17, R18, R19, R20, R22, R23, R24, R25, R26, R27: R-EU_0411/3V; 0411V
R3, R12, R21: R-EU_0207/10; 0207/10
U$1, U$2, U$3: TB6560-H; ZIP25-H

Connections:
+24V: C3.2, C5.2, C10.2, U$1.8 (VMB), U$1.18 (VMA), U$2.8 (VMB), U$2.18 (VMA), U$3.8 (VMB), U$3.18 (VMA)
ENABLE: JP1.2, JP2.2, JP4.2, U$1.4 (ENBL), U$2.4 (ENBL), U$3.4 (ENBL)
GND: C1.1, C2.1, C3.1, C4.1, C5.1, C6.2, C7.2, C8.1, C9.1, C10.1, C11.2, C12.1, JP1.1, JP2.1, JP4.1, R1.1, R2.1, R4.1, R5.1, R6.1, R7.1, R8.1, R9.1, R10.1, R11.1, R13.1, R14.1, R15.1, R16.1, R17.1, R18.1, R19.1, R20.1, R22.1, R23.1, R24.1, R25.1, R26.1, R27.1, U$1.2 (TQ1), U$1.6 (S-GND), U$1.10 (GND-B), U$1.15 (GND-A), U$1.23 (M1), U$1.24 (DCY-2), U$1.25 (DCY-1), U$2.2 (TQ1), U$2.6 (S-GND), U$2.10 (GND-B), U$2.15 (GND-A), U$2.23 (M1), U$2.24 (DCY-2), U$2.25 (DCY-1), U$3.2 (TQ1), U$3.6 (S-GND), U$3.10 (GND-B), U$3.15 (GND-A), U$3.23 (M1), U$3.24 (DCY-2), U$3.25 (DCY-1)
unnamed: R1.2, R4.2, R5.2, R6.2, U$1.14 (SENS-A)
unnamed: R2.2, R7.2, R8.2, R9.2, U$1.11 (SENS-B)
unnamed: JP3.1, U$1.16 (OUT-AP)
unnamed: JP3.3, U$1.12 (OUT-BP)
unnamed: JP3.2, U$1.13 (OUT-AM)
unnamed: JP3.4, U$1.9 (OUT-BM)
unnamed: R10.2, R13.2, R14.2, R15.2, U$2.14 (SENS-A)
unnamed: R11.2, R16.2, R17.2, R18.2, U$2.11 (SENS-B)
unnamed: JP5.1, U$2.16 (OUT-AP)
unnamed: C8.2, U$2.7 (OSC)
unnamed: R19.2, R22.2, R23.2, R24.2, U$3.14 (SENS-A)
unnamed: R20.2, R25.2, R26.2, R27.2, U$3.11 (SENS-B)
unnamed: C2.2, U$1.7 (OSC)
unnamed: C6.1, R12.1, U$2.5 (_RESET)
unnamed: JP5.3, U$2.12 (OUT-BP)
unnamed: JP5.2, U$2.13 (OUT-AM)
unnamed: JP5.4, U$2.9 (OUT-BM)
unnamed: JP6.1, U$3.16 (OUT-AP)
unnamed: C12.2, U$3.7 (OSC)
unnamed: C11.1, R21.1, U$3.5 (_RESET)
unnamed: JP6.3, U$3.12 (OUT-BP)
unnamed: C7.1, R3.1, U$1.5 (_RESET)
unnamed: JP6.2, U$3.13 (OUT-AM)
unnamed: JP6.4, U$3.9 (OUT-BM)
VCC: C1.2, C4.2, C9.2, R3.2, R12.2, R21.2, U$1.1 (TQ2), U$1.20 (VDD), U$1.22 (M2), U$2.1 (TQ2), U$2.20 (VDD), U$2.22 (M2), U$3.1 (TQ2), U$3.20 (VDD), U$3.22 (M2)
XDIR: JP4.3, U$1.21 (DIR)
XSTEP: JP4.4, U$1.3 (CLK)
YDIR: JP1.3, U$2.21 (DIR)
YSTEP: JP1.4, U$2.3 (CLK)
ZDIR: JP2.3, U$3.21 (DIR)
ZSTEP: JP2.4, U$3.3 (CLK)

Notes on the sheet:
Step
Dir
Enable
GND
0.5ohm=1A
0.25ohm=2A
TB6560AHQ

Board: 2 copper layers, 48 parts (0 on the bottom side), 34 nets, no tracks yet.

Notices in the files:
OPHW-EL-3DPElectronics/RAMPS1.5/RAMPS_1-3i.sch:
Copyright 2011 Johnny Russell
GPL v3
parts and their libraries:
SparkFun-Passives: Licensing: CC v3.0 Share-Alike You are welcome to use this library for commercial purposes.
SparkFun-Connectors: Licensing: Creative Commons ShareAlike 4.0 International - https://creativecommons.org/licenses/by-sa/4.0
